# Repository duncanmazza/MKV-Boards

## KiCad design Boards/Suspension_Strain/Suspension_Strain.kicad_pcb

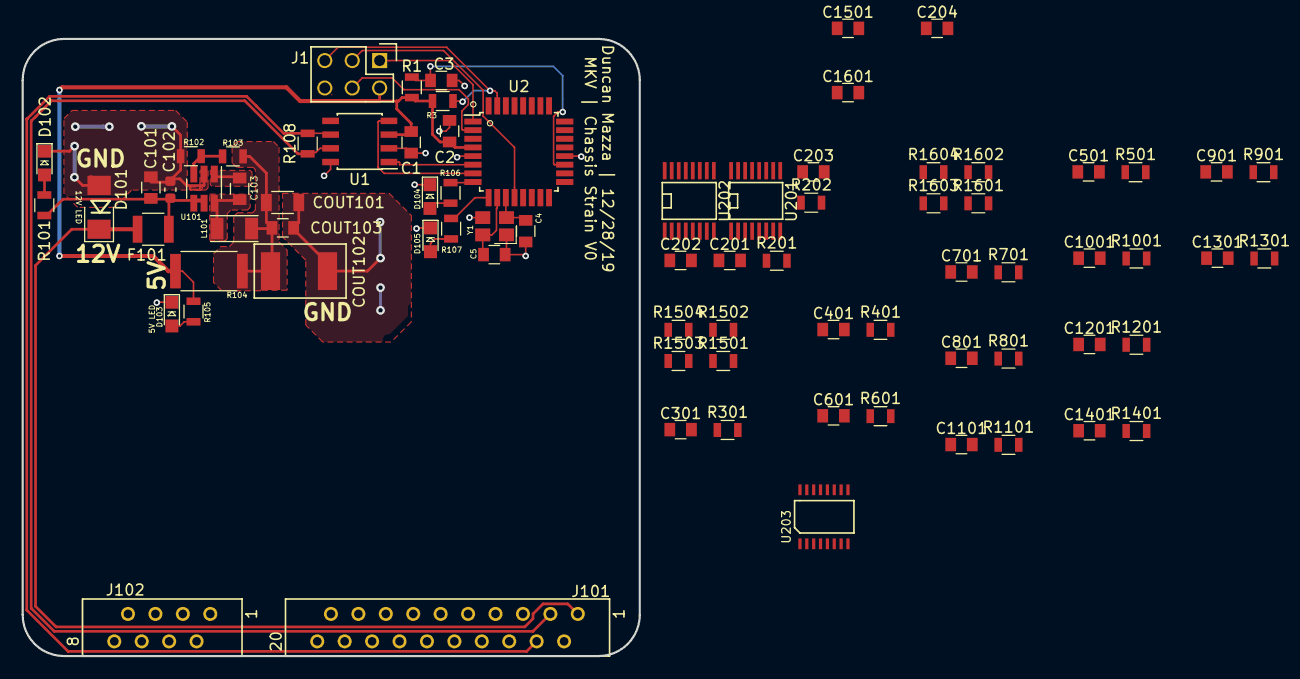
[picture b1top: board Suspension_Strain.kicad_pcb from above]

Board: 2 copper layers, 57.2 x 57.2 mm, 78 parts (0 on the bottom side), 53 nets.

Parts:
C1, C2, C101, C103, C201, C202, C203, C204, C301, C401, C501, C601, C701, C801, C901, C1001, C1101, C1201, C1301, C1401, C1501, C1601: C_0.1uF; C_0805_OEM
C3: C_100pF; C_0805_OEM
C4, C5: C_30pF; C_0805_OEM
C102: C_2.2uF; C_0603_1608Metric
COUT101: C_22uF; C_1206_OEM
COUT102: C_33uF; Fuse_1812
COUT103: C_47uF; C_0805_OEM
D101: D_Zener_18V; DO-214AA
D102, D103, D104, D105: LED_0805; LED_0805_OEM
F101: F_500mA_16V; Fuse_1210
J1: CONN_02X03; Pin_Header_Straight_2x03
J101: MM_F_RA_20; micromatch_female_ra_20
J102: MM_F_RA_08; micromatch_female_ra_8
L101: L_100uH; L_100uH_OEM
R1: R_100; R_0805_OEM
R3: R_10K; R_0805_OEM
R101: R_1K; R_0805_OEM
R102: R_25K; R_0805_OEM
R103: R_100K; R_0805_OEM
R104: R_0_2512; R_2512_OEM
R105, R106, R107: R_200; R_0805_OEM
R108: R_120_DNP; R_0805_OEM
R201, R202, R301, R401, R501, R601, R701, R801, R901, R1001, R1101, R1201, R1301, R1401, R1501, R1502, R1601, R1602: R_120; R_0805_OEM
R1503, R1504, R1603, R1604: R_120K; R_0805_OEM
U1: MCP2561-E_SN; SOIC-8_3.9x4.9mm_Pitch1.27mm_OEM
U2: ATMEGA16M1; TQFP-32_7x7mm_Pitch0.8mm
U101: TPS560430YF; SOT-23-6_Handsoldering
U201, U202: 74HC4051; TSSOP-16-OEM
U203: LTC6079CGN-PBF; SSOP-16_LTC1380
Y1: Crystal_SMD; Crystal_SMD_FA238

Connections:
/12V: D101.1, F101.2, J101.1
/CAN_+: J101.3, R108.1, U1.7
/CAN_-: J101.4, R108.2, U1.6
/CAN_RX: U1.4, U2.7
/CAN_TX: U1.1, U2.6
/MISO: J1.1, U2.1
/MOSI: J1.4, U2.2
/RESET: J1.5, R3.2, U2.31
/SCK: J1.3, U2.12
/amp_1_out: R1504.1, U2.28
/amp_2_out: R1604.1, U2.26
/mux_1_out: R1501.2, U203.6, U203.7
/mux_2_out: R1601.2, U203.15, U203.16
/mux_enable_input: U2.17, U201.8, U202.6
/mux_select_S0: U2.18, U201.3, U202.11
/mux_select_S1: U2.22, U201.16, U202.10
/mux_select_S2: U2.25, U201.7, U202.9
/ref_out: R1502.2, R1602.2, U203.1, U203.2
/wsb_container/mux_1_to_amp: U201.11, U203.5
/wsb_container/mux_2_to_amp: U202.3, U203.14
/wsb_container/ref: R201.2, R202.1, U203.3
/wsb_container/s1_+: J101.5, R301.1, U201.4
/wsb_container/s2_+: J101.7, R401.1, U201.2
/wsb_container/s3_+: J101.9, R501.1, U201.5
/wsb_container/s4_+: J101.11, R601.1, U201.1
/wsb_container/s5_+: J101.13, R701.1, U201.12
/wsb_container/s6_+: J101.15, R801.1, U201.15
/wsb_container/s7_+: J101.17, R901.1, U202.13
/wsb_container/s8_+: J101.19, R1001.1, U202.14
/wsb_container/s9_+: J102.1, R1101.1, U202.15
/wsb_container/s10_+: J102.3, R1201.1, U202.12
/wsb_container/s11_+: J102.5, R1301.1, U202.1
/wsb_container/s12_+: J102.7, R1401.1, U202.5
GND: C1.2, C2.2, C3.2, C4.2, C5.2, C101.2, C102.2, C201.2, C202.2, C203.2, C204.2, C301.2, C401.2, C501.2, C601.2, C701.2, C801.2, C901.2, C1001.2, C1101.2, C1201.2, C1301.2, C1401.2, C1501.2, C1601.2, COUT101.2, COUT102.2, COUT103.2, D101.2, D102.1, D103.1, D104.1, D105.1, J1.6, J101.2, J101.6, J101.8, J101.10, J101.12, J101.14, J101.16, J101.18, J101.20, J102.2, J102.4, J102.6, J102.8, R102.2, R202.2, R1503.2, R1603.2, U1.2, U1.8, U2.5, U2.20, U101.2, U201.6, U201.9, U202.7, U202.8, U203.13, Y1.2, Y1.4
unnamed: C3.1, R1.2, U2.19
unnamed: C4.1, U2.11, Y1.1
unnamed: C5.1, U2.10, Y1.3
unnamed: C101.1, C102.1, F101.1, R101.1, U101.4, U101.5
unnamed: C103.1, U101.1
unnamed: C103.2, L101.1, U101.6
unnamed: COUT101.1, COUT102.1, COUT103.1, L101.2, R103.1, R104.1
unnamed: D102.2, R101.2
unnamed: D103.2, R105.2
unnamed: D104.2, R106.1
unnamed: D105.2, R107.1
unnamed: R102.1, R103.2, U101.3
unnamed: R106.2, U2.8
unnamed: R107.2, U2.9
unnamed: R1501.1, R1503.1
unnamed: R1502.1, R1504.2
unnamed: R1601.1, R1603.1
unnamed: R1602.1, R1604.2
VCC: C1.1, C2.1, C201.1, C202.1, C203.1, C204.1, C301.1, C401.1, C501.1, C601.1, C701.1, C801.1, C901.1, C1001.1, C1101.1, C1201.1, C1301.1, C1401.1, C1501.1, C1601.1, J1.2, R1.1, R3.1, R104.2, R105.1, R201.1, R301.2, R401.2, R501.2, R601.2, R701.2, R801.2, R901.2, R1001.2, R1101.2, R1201.2, R1301.2, R1401.2, U1.3, U2.4, U201.10, U202.16, U203.4

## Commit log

2020-04-11 Restore missing contents of file
2020-04-11 Remove excessive differential amplifiers
2020-05-31 Add in-progress changes for reducing noise and component use
